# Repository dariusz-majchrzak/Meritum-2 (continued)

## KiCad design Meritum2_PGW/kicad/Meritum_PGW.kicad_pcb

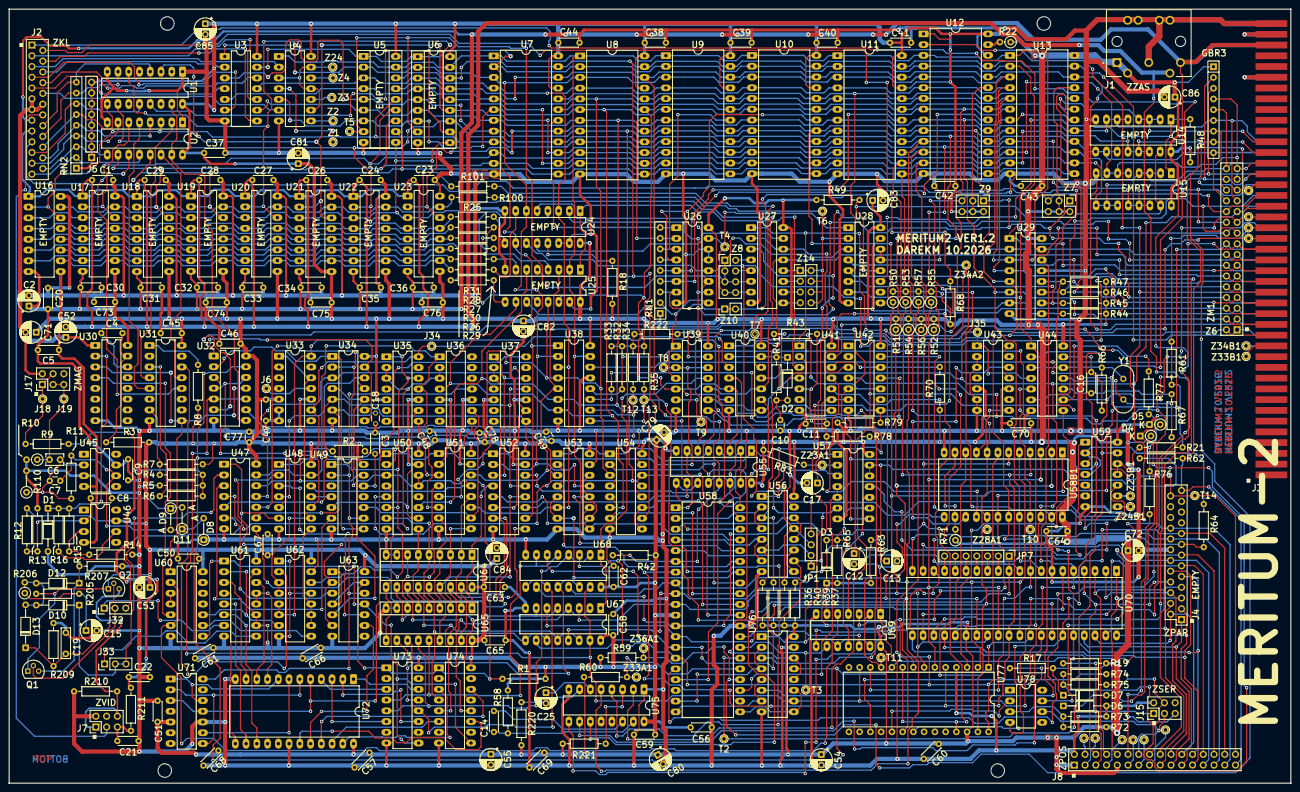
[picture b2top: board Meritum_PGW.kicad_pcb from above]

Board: 4 copper layers, 303.0 x 183.0 mm, 331 parts (0 on the bottom side), 330 nets.

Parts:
C1, C20, C23, C24, C26, C27, C28, C29, C30, C31, C32, C33, C34, C35, C36, C37, C38, C39, C40, C41, C42, C43, C44, C45, C46, C47, C50, C51, C56, C57, C58, C59, C60, C61, C62, C63, C64, C65, C66, C67, C68, C69, C70, C73, C74, C75, C76: 100n; c_200
C2, C12, C13, C17, C52, C53, C54, C55, C71, C72, C79, C80, C81, C82, C83, C84, C85, C86: 100uF; CP_Radial_D5.0mm_P2.50mm
C3, C11, C14, C16: 1n; c_200
C4: 33n; c_200
C5: 1u; c_200
C6: 10n; C_Rect_L4.0mm_W2.5mm_P2.50mm
C7: 330P; c_100
C8: 4u7; c_200
C9, C21, C22: 47n; c_200
C10: 470pF; c_100
C15: 22uF; CP_Radial_D5.0mm_P2.50mm
C18: 4n7; c_100
C19: 12p; C_Rect_L7.0mm_W2.0mm_P5.00mm
C25: 68uF; CP_Radial_D5.0mm_P2.50mm
C48, C49, C77, C78: 100n; c_100
D1, D2: 1N4148; D_DO-35_SOD27_P10.16mm_Horizontal
D3: BAYP95A; D_DO-35_SOD27_P10.16mm_Horizontal
D4, D5: 1N4148WT; D_DO-35_SOD27_P2.54mm_Vertical_KathodeUp
D6, D7, D10, D12, D13: 1N4148WT; D_DO-35_SOD27_P10.16mm_Horizontal
D8, D9, D11: 1N4148; D_DO-35_SOD27_P5.08mm_Vertical_AnodeUp
GBR3: 1K; R_Array_SIP9
J1: ZAS; CUI_SDS-50J
J2: ZKL; PinSocket_25_P2.54mm_Vertical
J3: ZM; Meritum_ZM
J4: ZPAR; PinSocket_25_P2.54mm_Vertical
J5: I; PinHeader_1x08_P2.54mm_Vertical
J6, J18, J19, J34, J35: T18; pin
J7: ZVID; PinHeader_2x03_P2.54mm_Vertical
J8: ZPOS; PinSocket_2x16_P2.54mm_Vertical_Meritum
J15: ZSER1; PinHeader_2x03_P2.54mm_Vertical
J17: ZMAG; PinHeader_2x03_P2.54mm_Vertical
J32, J33: Conn_01x03; PinHeader_1x03_P2.54mm_Vertical
JP1: Conn_01x04; PinHeader_1x04_P2.54mm_Vertical
JP7: Conn_01x07; PinHeader_1x07_P2.54mm_Vertical
Q1, Q2: BC550; TO-92L
R1, R8, R17, R19, R21, R32, R33, R34, R35, R36, R37, R39, R40, R44, R45, R46, R47, R48, R49, R64, R68, R70, R75, R79, R83, R221, R222: 1K; r_400
R2: 100; R_Axial_DIN0207_L6.3mm_D2.5mm_P7.62mm_Horizontal
R3, R220: 36K; r_400
R4, R6: 7K5; r_400
R5: 1K2; r_400
R7: 240k; r_400
R9, R72: 3K3; r_400
R10: 91K; R_Axial_DIN0207_L6.3mm_D2.5mm_P2.54mm_Vertical
R11: 240K; r_400
R12: 6K8; r_400
R13: 110; r_400
R14: 390; r_400
R15: 47K; r_400
R16: 150; r_400
R18, R58, R63, R65, R78: 10K; r_400
R22, R71: 1K; R_Axial_DIN0207_L6.3mm_D2.5mm_P2.54mm_Vertical
R25, R26, R27, R28, R29, R30, R31, R100, R101: 22; r_400
R41: 10k; r_400
R42, R66, R67: 330; r_400
R43, R62: 220; r_400
R50, R51, R52, R53, R54, R55, R56, R57: 15K; R_Axial_DIN0207_L6.3mm_D2.5mm_P2.54mm_Vertical
R59, R60, R209: 4K7; r_400
R61: 4k7; r_400
R73: 1K6; r_400
R74: 5K1; r_400
R76, R77: 270; r_400
R110: 4k7; R_Axial_DIN0207_L6.3mm_D2.5mm_P5.08mm_Vertical
R205: 2K2; r_400
R206: 2K2; R_Axial_DIN0207_L6.3mm_D2.5mm_P2.54mm_Vertical
R207: 2K; r_400
R210, R211: 100; r_400
RN1, RN2: 1K; R_Array_SIP9
T1, T4, T5, T6, T7, T8, T9, T10, T11, T12, T13, T14, T15, T16, T17, T18, T19: T18; pin
T2, T3: TP; pin
U1, U2, U67, U68: 8226; DIP-16_W7.62mm_LongPads
U3, U4, U42: 74LS06; DIP-14_W7.62mm_LongPads
U5, U6, U64, U65: 2114; DIP-18_W7.62mm_Socket_LongPads
U7, U8, U9, U10, U11, U13: 2716; DIP-24_W15.24mm_LongPads
U12: 2764_v1; DIP-28_W15.24mm_LongPads
U14, U15, U53, U54, U55, U56, U76: 8216; DIP-16_W7.62mm_LongPads
U16, U17, U18, U19, U20, U21, U22, U23: MK4116N; DIP-16_W7.62mm_LongPads
U24, U25, U50, U51, U52: 74LS157; DIP-16_W7.62mm_LongPads
U26: 74S188; DIP-16_W7.62mm_LongPads
U27: 74LS155; DIP-16_W7.62mm_LongPads
U28, U29, U38: 74S287; DIP-16_W7.62mm_LongPads
U30, U75: 74LS123; DIP-16_W7.62mm_LongPads
U31, U73, U74: 74LS175; DIP-16_W7.62mm_LongPads
U32, U39: 74LS32; DIP-14_W7.62mm_LongPads
U33: 74LS92; DIP-14_W7.62mm_LongPads
U34: 74LS10; DIP-14_W7.62mm_LongPads
U35, U36, U37, U71: 74LS93; DIP-14_W7.62mm_LongPads
U40, U44, U47: 74LS04; DIP-14_W7.62mm_LongPads
U41, U57: 74LS132; DIP-14_W7.62mm_LongPads
U43: 74LS90; DIP-14_W7.62mm_LongPads
U45, U46, U78: LM741; DIP-8_W7.62mm_LongPads
U48: 74LS08; DIP-14_W7.62mm_LongPads
U49: 74LS20; DIP-14_W7.62mm_LongPads
U58: Z80CPU; DIP-40_W15.24mm_LongPads
U58B1: 8253; DIP-24_W15.24mm_LongPads
U59, U63: 74LS74; DIP-14_W7.62mm_LongPads
U60: 74LS00; DIP-14_W7.62mm_LongPads
U61: 74LS165; DIP-16_W7.62mm_LongPads
U62: 74LS153; DIP-16_W7.62mm_LongPads
U69: 74LS125; DIP-14_W7.62mm_LongPads
U70: 8255; DIP-40_W15.24mm_LongPads
U72: 2732; DIP-24_W15.24mm_LongPads
U77: P8251A; DIP-28_W15.24mm
Y1: 10MHz; Crystal_HC49-4H_Vertical
Z1, Z2, Z3, Z4, Z23A1, Z23B1, Z24, Z24B1, Z28A1, Z33A1, Z33B1, Z34A2, Z34B1, Z36A1, Z36B1, Z37B1, Z38B1, Z39B1: TP; pin
Z6: ZM1; PinSocket_2x16_P2.54mm_Vertical_Meritum
Z7: Z3; PinHeader_2x03_P2.54mm_Vertical
Z8, Z14: Conn_02x04_Odd_Even; PinHeader_2x04_P2.54mm_Vertical
Z9: Z4; PinHeader_2x03_P2.54mm_Vertical
Z10: Conn_01x02; PinHeader_1x02_P2.54mm_Vertical

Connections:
+5V: C37.1, C38.1, C39.1, C40.1, C41.1, C42.1, C43.1, C44.1, C45.1, C46.1, C47.1, C48.1, C49.1, C50.1, C51.1, C53.1, C54.1, C55.1, C56.1, C57.1, C58.1, C59.1, C60.1, C61.1, C62.1, C63.1, C64.1, C65.1, C66.1, C67.1, C68.1, C69.1, C70.1, C71.1, C72.1, C73.1, C74.1, C75.1, C76.1, C77.1, C78.1, C79.1, C80.1, C81.1, C82.1, C83.1, C84.1, C85.1, C86.1, D3.1 (K), D5.1 (K), D7.1 (K), GBR3.1 (common), J1.1, J1.4, J4.8, J5.1, J5.2, J5.3, J5.4, J5.5, J5.6, J5.7, J5.8, J8.1, J8.9, Q1.1 (C), Q2.1 (C), R1.1, R3.1, R7.1, R8.2, R12.1, R17.2, R18.2, R19.1, R21.1, R22.1, R32.1, R33.1, R34.1, R35.1, R36.1, R37.1, R39.1, R40.1, R42.1, R44.1, R45.1, R46.1, R47.1, R48.1, R49.1, R50.2, R51.2, R52.2, R53.2, R54.2, R55.2, R56.2, R57.2, R58.2, R59.1, R60.1, R61.1, R63.1, R64.1, R65.1, R68.1, R70.2, R71.1, R72.1, R78.1, R79.1, R83.1, R205.1, R220.2, R221.2, R222.1, RN1.1 (common), RN2.1 (common), U1.16 (VCC), U2.16 (VCC), U3.14 (VCC), U4.14 (VCC), U5.18 (VCC), U6.18 (VCC), U7.21 (VPP), U7.24 (VCC), U8.21 (VPP), U8.24 (VCC), U9.21 (VPP), U9.24 (VCC), U10.21 (VPP), U10.24 (VCC), U11.21 (VPP), U11.24 (VCC), U12.1 (VPP), U12.23 (A11), U12.26 (NC), U12.28 (VCC), U13.21 (VPP), U13.24 (VCC), U14.16 (VCC), U15.16 (VCC), U16.9 (VCC), U17.9 (VCC), U18.9 (VCC), U19.9 (VCC), U20.9 (VCC), U21.9 (VCC), U22.9 (VCC), U23.9 (VCC), U24.16 (VCC), U25.16 (VCC), U26.16 (VCC), U27.16 (VCC), U28.16 (VCC), U29.16 (VCC), U30.16 (VCC), U31.16 (VCC), U32.14 (VCC), U33.5 (VCC), U34.14 (VCC), U35.5 (VCC), U36.5 (VCC), U37.5 (VCC), U38.16 (VCC), U39.14 (VCC), U40.14 (VCC), U41.14 (VCC), U42.14 (VCC), U43.5 (VCC), U44.14 (VCC), U46.7 (V+), U47.14 (VCC), U48.14 (VCC), U49.14 (VCC), U50.16 (VCC), U51.16 (VCC), U52.16 (VCC), U53.16 (VCC), U54.16 (VCC), U55.16 (VCC), U56.16 (VCC), U57.14 (VCC), U58.11 (VCC), U58B1.24 (VCC), U59.14 (VCC), U60.14 (VCC), U61.16 (VCC), U62.16 (VCC), U63.14 (VCC), U64.18 (VCC), U65.18 (VCC), U67.16 (VCC), U68.16 (VCC), U69.14 (VCC), U70.26 (VCC), U71.5 (VCC), U72.24 (VCC), U73.16 (VCC), U74.16 (VCC), U75.16 (VCC), U76.16 (VCC), U77.26 (VCC), Z7.2, Z7.3, Z7.4, Z7.6, Z9.2, Z9.3, Z9.4, Z9.6
+6V: J3.A42 (Pin_a42), J3.B42 (Pin_b42)
+12V: C2.1, C5.1, C9.2, C20.1, C22.1, C30.1, C31.1, C32.1, C33.1, C34.1, C35.1, C36.1, J1.3, J2.8, J3.A41 (Pin_a41), J3.B41 (Pin_b41), R211.2, U16.8 (VDD), U17.8 (VDD), U18.8 (VDD), U19.8 (VDD), U20.8 (VDD), U21.8 (VDD), U22.8 (VDD), U23.8 (VDD), U45.7 (V+), U78.7 (V+)
-5V: C1.2, C5.2, C23.2, C24.2, C26.2, C27.2, C28.2, C29.2, C52.2, J1.5, J2.9, U16.1 (VBB), U17.1 (VBB), U18.1 (VBB), U19.1 (VBB), U20.1 (VBB), U21.1 (VBB), U22.1 (VBB), U23.1 (VBB), U45.4 (V-), U46.4 (V-), U78.4 (V-)
-6V: J3.A38 (Pin_a38), J3.B38 (Pin_b38)
/CPU/Z0: U54.12 (DI3), U54.14 (DO3), U58.30 (A0)
/CPU/Z1: U54.9 (DI2), U54.11 (DO2), U58.31 (A1)
/CPU/Z2: U54.5 (DO1), U54.7 (DI1), U58.32 (A2)
/CPU/Z3: U54.2 (DO0), U54.4 (DI0), U58.33 (A3)
/CPU/Z4: U53.5 (DO1), U53.7 (DI1), U58.34 (A4)
/CPU/Z5: U53.2 (DO0), U53.4 (DI0), U58.35 (A5)
/CPU/Z6: U53.12 (DI3), U53.14 (DO3), U58.36 (A6)
/CPU/Z7: U53.9 (DI2), U53.11 (DO2), U58.37 (A7)
/CPU/Z8: U55.9 (DI2), U55.11 (DO2), U58.38 (A8)
/CPU/Z9: U55.12 (DI3), U55.14 (DO3), U58.39 (A9)
/CPU/Z10: U55.2 (DO0), U55.4 (DI0), U58.40 (A10)
/CPU/Z11: U55.5 (DO1), U55.7 (DI1), U58.1 (A11)
/CPU/Z12: U56.2 (DO0), U56.4 (DI0), U58.2 (A12)
/CPU/Z13: U56.12 (DI3), U56.14 (DO3), U58.3 (A13)
/CPU/Z14: U56.5 (DO1), U56.7 (DI1), U58.4 (A14)
/CPU/Z15: U56.9 (DI2), U56.11 (DO2), U58.5 (A15)
/Display/BLANK: U63.9 (Q), U72.20 (~OE/VPP)
/Display/DD0: U65.14 (D0), U68.5 (DO1), U68.7 (DI1), U73.4 (D0)
/Display/DD1: U65.13 (D1), U68.2 (DO0), U68.4 (DI0), U73.5 (D1)
/Display/DD2: U65.12 (D2), U68.9 (DI2), U68.11 (DO2), U73.12 (D2)
/Display/DD3: U65.11 (D3), U68.12 (DI3), U68.14 (DO3), U73.13 (D3)
/Display/DD4: U64.14 (D0), U67.9 (DI2), U67.11 (DO2), U74.4 (D0)
/Display/DD5: U64.13 (D1), U67.12 (DI3), U67.14 (DO3), U74.5 (D1)
/Display/DD6: U64.12 (D2), U67.2 (DO0), U67.4 (DI0), U74.12 (D2)
/Display/DD7: U64.11 (D3), U67.5 (DO1), U67.7 (DI1), U74.13 (D3)
/Display/L0: U71.1 (CP1..3), U71.12 (Q0), U72.8 (A0)
/Display/L1: U71.9 (Q1), U72.7 (A1)
/Display/L2: U71.2 (R0(1)), U71.8 (Q2), U72.6 (A2)
/Display/L3: U37.14 (CP0), U71.3 (R0(2)), U71.11 (Q3), U72.5 (A3)
/Display/MA0: U50.7 (Zb), U64.5 (A0), U65.5 (A0)
/Display/MA1: U50.9 (Zc), U64.6 (A1), U65.6 (A1)
/Display/MA2: U51.4 (Za), U64.7 (A2), U65.7 (A2)
/Display/MA3: U51.7 (Zb), U64.4 (A3), U65.4 (A3)
/Display/MA4: U51.9 (Zc), U64.3 (A4), U65.3 (A4)
/Display/MA5: U51.12 (Zd), U64.2 (A5), U65.2 (A5)
/Display/MA6: U52.4 (Za), U64.1 (A6), U65.1 (A6)
/Display/MA7: U52.7 (Zb), U64.17 (A7), U65.17 (A7)
/Display/MA8: U52.9 (Zc), U64.16 (A8), U65.16 (A8)
/Display/MA9: U52.12 (Zd), U64.15 (A9), U65.15 (A9)
/Display/NET_R1: R1.2, U34.2, U50.3 (I1a), U50.13 (I1d), U50.14 (I0d), U63.1 (~R), U63.4 (~S), U63.13 (~R), U73.1 (~Mr), U74.1 (~Mr)
/Display/SYNC: J32.3, U47.1, U48.6
/Display/VID_OUT: J7.1, J7.6, Q2.3 (E), R210.1
/Display/X0: U35.1 (CP1..3), U35.12 (Q0), U49.1, U50.6 (I1b), U62.14 (S0)
/Display/X1: U35.9 (Q1), U49.5, U50.10 (I1c)
/Display/X2: U35.8 (Q2), U51.3 (I1a)
/Display/X3: U35.11 (Q3), U36.1 (CP1..3), U47.13, U48.13, U51.6 (I1b)
/Display/X4: U36.9 (Q1), U49.10, U51.10 (I1c)
/Display/X5: U36.8 (Q2), U48.12, U51.13 (I1d)
/Display/X6: U37.1 (CP1..3), U37.12 (Q0), U52.3 (I1a)
/Display/X7: U34.3, U37.9 (Q1), U47.11, U52.6 (I1b)
/Display/X8: U34.9, U37.8 (Q2), U52.10 (I1c)
/Display/X9: U34.5, U37.11 (Q3), U47.5, U52.13 (I1d)
/Display/Y1: U36.11 (Q3), U49.2, U49.9, U63.12 (D), U71.14 (CP0)
/Display/Y2: U34.4, U34.10, U63.5 (Q)
/Display/~LOAD: U60.8, U61.1 (~PL), U63.11 (C), U73.9 (Cp), U74.9 (Cp)
/Display/~Y2: U48.2, U63.2 (D), U63.6 (~Q)
/Interface/CTS: J8.16, J15.4, R75.1
/Interface/KA0: J2.5, U3.4
/Interface/KA1: J2.15, U3.8
/Interface/KA2: J2.18, U4.6
/Interface/KA3: J2.4, U3.6
/Interface/KA4: J2.2, U3.10
/Interface/KA5: J2.16, U3.2
/Interface/KA6: J2.17, U3.12
/Interface/KA7: J2.3, U4.2
/Interface/KD0: J2.24, RN2.5 (R4), U2.4 (DI0)
/Interface/KD1: J2.12, RN2.4 (R3), U2.7 (DI1)
/Interface/KD2: J2.25, RN2.3 (R2), U2.9 (DI2)
/Interface/KD3: J2.13, RN2.2 (R1), U2.12 (DI3)
/Interface/KD4: J2.22, RN2.8 (R7), U1.7 (DI1)
/Interface/KD5: J2.21, RN2.9 (R8), U1.4 (DI0)
/Interface/KD6: J2.23, RN2.6 (R5), U1.9 (DI2)
/Interface/KD7: J2.11, RN2.7 (R6), U1.12 (DI3)
/Interface/PA0: J4.17, J8.6, U70.4 (PA0)
/Interface/PA1: J4.4, J8.8, U70.3 (PA1)
/Interface/PA2: J4.16, J8.20, U70.2 (PA2)
/Interface/PA3: J4.3, J8.10, U70.1 (PA3)
/Interface/PA4: J4.2, J8.21, U70.40 (PA4)
/Interface/PA5: J4.15, J8.17, U70.39 (PA5)
/Interface/PA6: J4.14, J8.22, U70.38 (PA6)
/Interface/PA7: J4.1, J8.19, U70.37 (PA7)
/Interface/PB0: J4.9, J8.30, U70.18 (PB0)
/Interface/PB1: J4.7, J8.28, U70.19 (PB1)
/Interface/PB2: J4.21, J8.27, U70.20 (PB2)
/Interface/PB3: J4.22, J8.29, U70.21 (PB3)
/Interface/PB4: J4.6, J8.26, U70.22 (PB4)
/Interface/PB5: J4.19, J8.25, U70.23 (PB5)
/Interface/PB6: J4.18, J8.23, U70.24 (PB6)
/Interface/PB7: J4.5, J8.24, U70.25 (PB7)
/Interface/PC0: J8.4, JP7.4, T15.1 (Pin_1_1), U70.14 (PC0)
/Interface/PC1: J8.3, JP7.5, T1.1 (Pin_1_1), U70.15 (PC1)
/Interface/PC2: J8.13, JP7.6, T17.1 (Pin_1_1), U70.16 (PC2)
/Interface/PC3: J8.7, JP7.7, T16.1 (Pin_1_1), U70.17 (PC3)
/Interface/PC4: J8.11, JP7.3, T18.1 (Pin_1_1), U70.13 (PC4)
/Interface/PC5: J8.15, JP7.2, T19.1 (Pin_1_1), U70.12 (PC5)
/Interface/PC6: JP7.1, U70.11 (PC6), U75.11 (Clr)
/Interface/PC7: U42.13, U70.10 (PC7)
/Interface/R1K: J8.5, J15.1, R19.2
/Interface/REC: J8.12, J15.5, R76.1
/Interface/SIG_IN: C6.1, J17.3, J17.5, J19.1 (Pin_1_1), R10.1
/Interface/SIG_OUT: J17.1, J17.4, J18.1 (Pin_1_1), R9.1
/Interface/TR: J8.14, J15.3, U78.6
/MEM/E0: R31.1, U16.5 (A0), U17.5 (A0), U18.5 (A0), U19.5 (A0), U20.5 (A0), U21.5 (A0), U22.5 (A0), U23.5 (A0)
/MEM/E1: R30.1, U16.7 (A1), U17.7 (A1), U18.7 (A1), U19.7 (A1), U20.7 (A1), U21.7 (A1), U22.7 (A1), U23.7 (A1)
/MEM/E2: R29.1, U16.6 (A2), U17.6 (A2), U18.6 (A2), U19.6 (A2), U20.6 (A2), U21.6 (A2), U22.6 (A2), U23.6 (A2)
/MEM/E3: R28.1, U16.12 (A3), U17.12 (A3), U18.12 (A3), U19.12 (A3), U20.12 (A3), U21.12 (A3), U22.12 (A3), U23.12 (A3)
/MEM/E4: R27.1, U16.11 (A4), U17.11 (A4), U18.11 (A4), U19.11 (A4), U20.11 (A4), U21.11 (A4), U22.11 (A4), U23.11 (A4)
/MEM/E5: R26.1, U16.10 (A5), U17.10 (A5), U18.10 (A5), U19.10 (A5), U20.10 (A5), U21.10 (A5), U22.10 (A5), U23.10 (A5)
/MEM/E6: R25.1, U16.13 (A6), U17.13 (A6), U18.13 (A6), U19.13 (A6), U20.13 (A6), U21.13 (A6), U22.13 (A6), U23.13 (A6)
/MEM/U27P15: U24.12 (Zd), U27.15 (Eb2)
/MEM/~M1CS: RN1.9 (R8), U7.18 (~EP), U26.1 (Q0)
/MEM/~M2CS: RN1.8 (R7), U8.18 (~EP), U26.2 (Q1)
/MEM/~M3CS: RN1.7 (R6), U9.18 (~EP), U26.3 (Q2)
/MEM/~M4CS: RN1.6 (R5), U10.18 (~EP), U26.4 (Q3)
/MEM/~M5CS: RN1.5 (R4), U11.18 (~EP), U26.5 (Q4)
/MEM/~M6CS: RN1.4 (R3), U12.20 (~CE), U26.6 (Q5)
/MEM/~M7CS: RN1.3 (R2), U13.18 (~EP), U26.7 (Q6), Z10.1, Z10.2
/MEM/~RAS: R101.2, U16.4 (~RAS), U17.4 (~RAS), U18.4 (~RAS), U19.4 (~RAS), U20.4 (~RAS), U21.4 (~RAS), U22.4 (~RAS), U23.4 (~RAS)
A0: J3.B14 (Pin_b14), U3.3, U5.5 (A0), U6.5 (A0), U7.8 (A0), U8.8 (A0), U9.8 (A0), U10.8 (A0), U11.8 (A0), U12.10 (A0), U13.8 (A0), U25.3 (I1a), U29.5 (A0), U38.5 (A0), U50.5 (I0b), U54.13 (DB3), U58B1.19 (A0), U70.9 (A0), U77.12 (C/~D), Z6.2
A1: J3.B15 (Pin_b15), U3.9, U5.6 (A1), U6.6 (A1), U7.7 (A1), U8.7 (A1), U9.7 (A1), U10.7 (A1), U11.7 (A1), U12.9 (A1), U13.7 (A1), U25.6 (I1b), U29.6 (A1), U38.6 (A1), U50.11 (I0c), U54.10 (DB2), U58B1.20 (A1), U70.8 (A1), Z6.4
A2: J3.B16 (Pin_b16), U4.5, U5.7 (A2), U6.7 (A2), U7.6 (A2), U8.6 (A2), U9.6 (A2), U10.6 (A2), U11.6 (A2), U12.8 (A2), U13.6 (A2), U25.10 (I1c), U29.7 (A2), U38.7 (A2), U51.2 (I0a), U54.6 (DB1), Z6.6
A3: J3.B17 (Pin_b17), U3.5, U5.4 (A3), U6.4 (A3), U7.5 (A3), U8.5 (A3), U9.5 (A3), U10.5 (A3), U11.5 (A3), U12.7 (A3), U13.5 (A3), U25.13 (I1d), U29.4 (A3), U38.4 (A3), U51.5 (I0b), U54.3 (DB0), Z6.7
A4: J3.B18 (Pin_b18), U3.11, U5.3 (A4), U6.3 (A4), U7.4 (A4), U8.4 (A4), U9.4 (A4), U10.4 (A4), U11.4 (A4), U12.6 (A4), U13.4 (A4), U24.3 (I1a), U29.3 (A4), U38.3 (A4), U51.11 (I0c), U53.6 (DB1), Z6.10
A5: J3.B19 (Pin_b19), U3.1, U5.2 (A5), U6.2 (A5), U7.3 (A5), U8.3 (A5), U9.3 (A5), U10.3 (A5), U11.3 (A5), U12.5 (A5), U13.3 (A5), U24.6 (I1b), U29.2 (A5), U38.2 (A5), U51.14 (I0d), U53.3 (DB0), Z6.12
A6: J3.B20 (Pin_b20), U3.13, U5.1 (A6), U6.1 (A6), U7.2 (A6), U8.2 (A6), U9.2 (A6), U10.2 (A6), U11.2 (A6), U12.4 (A6), U13.2 (A6), U24.10 (I1c), U29.1 (A6), U38.1 (A6), U52.2 (I0a), U53.13 (DB3), Z6.13
A7: J3.B21 (Pin_b21), U4.1, U5.17 (A7), U6.17 (A7), U7.1 (A7), U8.1 (A7), U9.1 (A7), U10.1 (A7), U11.1 (A7), U12.3 (A7), U13.1 (A7), U25.2 (I0a), U29.15 (A7), U38.15 (A7), U52.5 (I0b), U53.10 (DB2), Z6.16
A8: J3.A14 (Pin_a14), U5.16 (A8), U6.16 (A8), U7.23 (A8), U8.23 (A8), U9.23 (A8), U10.23 (A8), U11.23 (A8), U12.25 (A8), U13.23 (A8), U25.5 (I0b), U52.11 (I0c), U55.10 (DB2), Z6.1
A9: J3.A15 (Pin_a15), U5.15 (A9), U6.15 (A9), U7.22 (A9), U8.22 (A9), U9.22 (A9), U10.22 (A9), U11.22 (A9), U12.24 (A9), U13.22 (A9), U25.11 (I0c), U52.14 (I0d), U55.13 (DB3), Z6.3
A10: J3.A16 (Pin_a16), U7.19 (A10), U8.19 (A10), U9.19 (A10), U10.19 (A10), U11.19 (A10), U12.21 (A10), U13.19 (A10), U25.14 (I0d), U39.5, U40.5, U55.3 (DB0), Z6.5
A11: J3.A17 (Pin_a17), U24.2 (I0a), U26.10 (A0), U55.6 (DB1), Z6.8, Z7.1, Z9.1
A12: J3.A18 (Pin_a18), JP1.4, R40.2, U12.2 (A12), U24.5 (I0b), U26.11 (A1), U56.3 (DB0), Z6.9
A13: J3.A19 (Pin_a19), JP1.3, R39.2, U24.11 (I0c), U26.12 (A2), U56.13 (DB3), Z6.11
A14: J3.A20 (Pin_a20), JP1.2, R36.2, U27.13 (A0), U56.6 (DB1), Z6.14
A15: J3.A21 (Pin_a21), JP1.1, R37.2, U27.3 (A1), U56.10 (DB2), Z6.15
BD0: GBR3.2 (R1), J3.B29 (Pin_b29), R57.1, U2.3 (DB0), U5.14 (D0), U7.9 (Q0), U8.9 (Q0), U9.9 (Q0), U10.9 (Q0), U11.9 (Q0), U12.11 (D0), U13.9 (Q0), U15.12 (DI3), U15.13 (DB3), U15.14 (DO3), U16.2 (DIN), U16.14 (DOUT), U58.14 (D0), U58B1.8 (D0), U68.6 (DB1), U70.34 (D0), U77.27 (D0), Z6.30
BD1: GBR3.4 (R3), J3.B30 (Pin_b30), R56.1, U2.6 (DB1), U5.13 (D1), U7.10 (Q1), U8.10 (Q1), U9.10 (Q1), U10.10 (Q1), U11.10 (Q1), U12.12 (D1), U13.10 (Q1), U15.5 (DO1), U15.6 (DB1), U15.7 (DI1), U17.2 (DIN), U17.14 (DOUT), U58.15 (D1), U58B1.7 (D1), U68.3 (DB0), U70.33 (D1), U77.28 (D1), Z6.31
BD2: GBR3.8 (R7), J3.B31 (Pin_b31), R55.1, U2.10 (DB2), U5.12 (D2), U7.11 (Q2), U8.11 (Q2), U9.11 (Q2), U10.11 (Q2), U11.11 (Q2), U12.13 (D2), U13.11 (Q2), U14.12 (DI3), U14.13 (DB3), U14.14 (DO3), U18.2 (DIN), U18.14 (DOUT), U58.12 (D2), U58B1.6 (D2), U68.10 (DB2), U70.32 (D2), U77.1 (D2), Z6.27
BD3: GBR3.7 (R6), J3.B32 (Pin_b32), R54.1, U2.13 (DB3), U5.11 (D3), U7.13 (Q3), U8.13 (Q3), U9.13 (Q3), U10.13 (Q3), U11.13 (Q3), U12.15 (D3), U13.13 (Q3), U14.2 (DO0), U14.3 (DB0), U14.4 (DI0), U19.2 (DIN), U19.14 (DOUT), U58.8 (D3), U58B1.5 (D3), U68.13 (DB3), U70.31 (D3), U77.2 (D3), Z6.28
BD4: GBR3.3 (R2), J3.A29 (Pin_a29), R53.1, U1.6 (DB1), U6.14 (D0), U7.14 (Q4), U8.14 (Q4), U9.14 (Q4), U10.14 (Q4), U11.14 (Q4), U12.16 (D4), U13.14 (Q4), U15.9 (DI2), U15.10 (DB2), U15.11 (DO2), U20.2 (DIN), U20.14 (DOUT), U58.7 (D4), U58B1.4 (D4), U67.10 (DB2), U70.30 (D4), U77.5 (D4), Z6.29
BD5: GBR3.5 (R4), J3.A30 (Pin_a30), R52.1, U1.3 (DB0), U6.13 (D1), U7.15 (Q5), U8.15 (Q5), U9.15 (Q5), U10.15 (Q5), U11.15 (Q5), U12.17 (D5), U13.15 (Q5), U15.2 (DO0), U15.3 (DB0), U15.4 (DI0), U21.2 (DIN), U21.14 (DOUT), U58.9 (D5), U58B1.3 (D5), U67.13 (DB3), U70.29 (D5), U77.6 (D5), Z6.32
BD6: GBR3.9 (R8), J3.A31 (Pin_a31), R51.1, U1.10 (DB2), U6.12 (D2), U7.16 (Q6), U8.16 (Q6), U9.16 (Q6), U10.16 (Q6), U11.16 (Q6), U12.18 (D6), U13.16 (Q6), U14.9 (DI2), U14.10 (DB2), U14.11 (DO2), U22.2 (DIN), U22.14 (DOUT), U58.10 (D6), U58B1.2 (D6), U67.3 (DB0), U70.28 (D6), U77.7 (D6), Z6.26
BD7: GBR3.6 (R5), J3.A32 (Pin_a32), R50.1, U1.13 (DB3), U6.11 (D3), U7.17 (Q7), U8.17 (Q7), U9.17 (Q7), U10.17 (Q7), U11.17 (Q7), U12.19 (D7), U13.17 (Q7), U14.5 (DO1), U14.6 (DB1), U14.7 (DI1), U23.2 (DIN), U23.14 (DOUT), U58.13 (D7), U58B1.1 (D7), U67.6 (DB1), U69.6, U70.27 (D7), U77.8 (D7), Z6.25
BUC: J4.25, J8.32, R47.2, T14.1 (Pin_1_1), U29.12 (Q1)
BUSAK: U42.9, U53.1 (~CS), U54.1 (~CS), U55.1 (~CS), U57.6, U69.10, U69.13, U76.1 (~CS)
CKPIX: U60.10, U61.2 (CP), U62.7 (Za)
FON: J2.20, J7.3
GND: C1.1, C2.2, C3.2, C9.1, C10.2, C11.2, C12.2, C13.2, C15.2, C17.2, C18.2, C19.2, C20.2, C21.2, C22.2, C23.1, C24.1, C26.1, C27.1, C28.1, C29.1, C30.2, C31.2, C32.2, C33.2, C34.2, C35.2, C36.2, C37.2, C38.2, C39.2, C40.2, C41.2, C42.2, C43.2, C44.2, C45.2, C46.2, C47.2, C48.2, C49.2, C50.2, C51.2, C52.1, C53.2, C54.2, C55.2, C56.2, C57.2, C58.2, C59.2, C60.2, C61.2, C62.2, C63.2, C64.2, C65.2, C66.2, C67.2, C68.2, C69.2, C70.2, C71.2, C72.2, C73.2, C74.2, C75.2, C76.2, C77.2, C78.2, C79.2, C80.2, C81.2, C82.2, C83.2, C84.2, C85.2, C86.2, D1.2 (A), D4.2 (A), D6.2 (A), D8.1 (K), J1.2, J1.SH, J2.6, J2.7, J2.19, J3.A43 (Pin_a43), J3.B43 (Pin_b43), J4.20, J7.2, J8.2, J15.2, J17.2, R5.1, R10.2, R13.2, R14.2, R73.2, R110.2, R207.2, R209.2, R210.2, U1.1 (~CS), U1.8 (GND), U2.1 (~CS), U2.8 (GND), U3.7 (GND), U4.7 (GND), U5.9 (GND), U6.9 (GND), U7.12 (GND), U8.12 (GND), U9.12 (GND), U10.12 (GND), U11.12 (GND), U12.14 (GND), U13.12 (GND), U14.8 (GND), U15.8 (GND), U16.16 (VSS), U17.16 (VSS), U18.16 (VSS), U19.16 (VSS), U20.16 (VSS), U21.16 (VSS), U22.16 (VSS), U23.16 (VSS), U24.8 (GND), U24.14 (I0d), U24.15 (E), U25.8 (GND), U25.15 (E), U26.8 (GND), U26.13 (A3), U26.14 (A4), U27.8 (GND), U28.8 (GND), U28.13 (~CE1), U28.14 (~CE2), U29.8 (GND), U29.13 (~CE1), U30.1 (A), U30.8 (GND), U31.8 (GND), U32.7 (GND), U33.6 (R0(1)), U33.7 (R0(2)), U33.10 (GND), U34.7 (GND), U35.10 (GND), U36.10 (GND), U37.10 (GND), U38.8 (GND), U38.13 (~CE1), U39.7 (GND), U40.7 (GND), U41.7 (GND), U42.7 (GND), U43.2 (R0(1)), U43.3 (R0(2)), U43.6 (R9(1)), U43.7 (R9(2)), U43.10 (GND), U44.7 (GND), U45.3 (+), U47.7 (GND), U48.7 (GND), U49.7 (GND), U50.8 (GND), U50.15 (E), U51.8 (GND), U51.15 (E), U52.8 (GND), U52.15 (E), U53.8 (GND), U53.15 (~DIEN), U54.8 (GND), U54.15 (~DIEN), U55.8 (GND), U55.15 (~DIEN), U56.8 (GND), U56.15 (~DIEN), U57.7 (GND), U58.29 (GND), U58B1.12 (GND), U59.7 (GND), U60.7 (GND), U61.8 (GND), U61.10 (DS), U61.11 (D0), U61.15 (~CE), U62.1 (Ea), U62.8 (GND), U62.13 (I3b), U62.15 (Eb), U63.7 (GND), U64.8 (~CS), U64.9 (GND), U65.8 (~CS), U65.9 (GND), U67.8 (GND), U68.8 (GND), U69.1, U69.7 (GND), U70.7 (GND), U71.10 (GND), U72.12 (GND), U72.18 (~CE), U73.8 (GND), U74.8 (GND), U75.1 (A), U75.8 (GND), U76.8 (GND), U76.15 (~DIEN), U77.4 (GND)
IE: J3.B25 (Pin_b25), Z39B1.1 (Pin_1_1)
MON: U31.14 (~Q3), U62.2 (S1)
NMIX: J2.14, R68.2, U41.13
unnamed: C3.1, R2.2, U49.12
unnamed: C11.1, R43.1, U41.5
unnamed: C13.1, R62.2, R63.2, U57.12, U57.13
unnamed: C15.1, R205.2, R206.1
unnamed: C16.1, R67.2, U44.10
unnamed: C16.2, R66.1, U44.13
unnamed: C17.1, R78.2, U41.9, U42.6
unnamed: C18.1, U34.6, U47.9
unnamed: D1.1 (K), R15.2, R16.2, U30.2 (B)
unnamed: C10.1, D2.2 (A), R41.2, U41.2
unnamed: D2.1 (K), R41.1, U40.2, U40.13
unnamed: C12.1, D3.2 (A), R65.2, U57.9
unnamed: D4.1 (K), D5.2 (A), R74.1, R75.2
unnamed: D6.1 (K), D7.2 (A), R76.2, R77.1
unnamed: D10.2 (A), D12.2 (A), D13.2 (A), R206.2
unnamed: D10.1 (K), J33.2, J33.3, U47.2
unnamed: C8.2, D9.1 (K), D11.2 (A)
unnamed: C7.2, D8.2 (A), D9.2 (A), D11.1 (K), R11.2, U45.6
unnamed: D12.1 (K), Q1.3 (E), R207.1
unnamed: C19.1, D13.1 (K), Q2.2 (B), R209.1
unnamed: J6.1 (Pin_1_1), U33.11 (Q1)
unnamed: C21.1, J7.5, R211.1
unnamed: J32.1, J32.2, Q1.2 (B), U61.7 (~Q7)
unnamed: J33.1, U61.9 (Q7)
unnamed: J34.1 (Pin_1_1), U33.9 (Q2), U35.14 (CP0), U40.3, U48.10
unnamed: R2.1, U47.12, U49.13
unnamed: R4.1, R5.2, R6.1, R9.2
unnamed: R16.1, U46.6
unnamed: R66.2, U44.3, U44.12, Y1.1
unnamed: R67.1, U44.11, Y1.2
unnamed: R70.1, U41.12, U42.12
unnamed: R77.2, U44.9
unnamed: R222.2, U39.13, U42.10
unnamed: RN1.2 (R1), U26.9 (Q7), U39.1, U39.4
unnamed: T3.1 (Pin_1_1), U58.27 (~M1), U69.9
unnamed: R101.1, T7.1 (Pin_1_1), U40.12
unnamed: U1.15 (~DIEN), U2.15 (~DIEN), U32.8
unnamed: U2.2 (DO0), U31.4 (D0)
unnamed: U2.5 (DO1), U31.5 (D1)
unnamed: U2.11 (DO2), U31.12 (D2)
unnamed: U2.14 (DO3), U31.13 (D3)
unnamed: R22.2, U12.27 (~PGM)
unnamed: R48.2, U14.1 (~CS), U15.1 (~CS), U28.11 (Q2)
unnamed: R49.2, U14.15 (~DIEN), U15.15 (~DIEN), U28.12 (Q1)
unnamed: R18.1, U24.13 (I1d)
unnamed: U24.1 (S), U25.1 (S), U41.3
unnamed: R27.2, U24.4 (Za)
unnamed: R26.2, U24.7 (Zb)
unnamed: R25.2, U24.9 (Zc)
unnamed: R31.2, U25.4 (Za)
unnamed: R30.2, U25.7 (Zb)
unnamed: R29.2, U25.9 (Zc)
unnamed: R28.2, U25.12 (Zd)
unnamed: U27.9 (Q0b), Z14.7
unnamed: U27.10 (Q1b), Z14.5
unnamed: U27.5 (Q2a), Z8.4
unnamed: U27.11 (Q2b), Z14.3
unnamed: U27.4 (Q3a), Z8.2
unnamed: C4.1, U30.14 (Cext)
unnamed: U30.3 (Clr), U31.9 (Cp), U32.11, U60.1
unnamed: C4.2, R3.2, U30.15 (RCext)
unnamed: U30.4 (~Q), U60.5
unnamed: R4.2, R7.2, U31.7 (Q1)
unnamed: R8.1, U31.1 (~Mr)
unnamed: R6.2, U31.3 (~Q0)
unnamed: U32.1, U34.8, U34.13
unnamed: U32.2, U34.1, U49.8
unnamed: U32.3, U48.5
unnamed: U32.6, U69.4
unnamed: U33.1 (CP1..3), U33.12 (Q0), U48.9, U62.3 (I3a), U62.4 (I2a)
unnamed: U34.11, U47.10
unnamed: U34.12, U48.4
unnamed: U35.2 (R0(1)), U35.3 (R0(2)), U36.2 (R0(1)), U36.3 (R0(2)), U47.4
unnamed: U37.2 (R0(1)), U37.3 (R0(2)), U47.8
unnamed: U39.2, U40.6
unnamed: U39.8, U42.11
unnamed: U43.11 (Q3), U43.14 (CP0)
unnamed: U43.12 (Q0), U58B1.15 (CLK1)
unnamed: U43.8 (Q2), U58B1.9 (CLK0)
unnamed: C6.2, C7.1, R11.1, R110.1, U45.2 (-)
unnamed: R14.1, R15.1, U46.3 (+)
unnamed: C8.1, R12.2, R13.1, U46.2 (-)
unnamed: U47.3, U49.6
unnamed: U48.11, U49.4
unnamed: U50.4 (Za), U64.10 (~WE), U65.10 (~WE)
unnamed: U56.1 (~CS), U57.3
unnamed: U57.4, U57.5, U58.23 (~BUSACK)
unnamed: U58.20 (~IORQ), U76.5 (DO1), U76.7 (DI1)
unnamed: U58.19 (~MREQ), U76.2 (DO0), U76.4 (DI0)
unnamed: U58.21 (~RD), U76.9 (DI2), U76.11 (DO2)
unnamed: U58.28 (~RFSH), U69.12
unnamed: U40.9, U58.22 (~WR), U76.12 (DI3), U76.14 (DO3)
unnamed: R71.2, U58B1.11 (G0), U58B1.14 (G1)
unnamed: U41.11, U58B1.16 (G2)
unnamed: U58B1.13 (OUT1), U75.9 (A)
unnamed: U44.2, U59.3 (C)
unnamed: R64.2, U59.2 (D), U59.4 (~S)
unnamed: U59.5 (Q), U75.2 (B)
unnamed: U57.11, U59.1 (~R)
unnamed: R21.2, U59.11 (C), U59.12 (D)
unnamed: U59.9 (Q), Z23B1.1 (Pin_1_1)
unnamed: U59.8 (~Q), Z24B1.1 (Pin_1_1)
unnamed: U60.2, U60.6, U69.5
unnamed: U60.3, U60.4
unnamed: U61.12 (D1), U61.13 (D2), U72.9 (Q0)
unnamed: U61.14 (D3), U72.10 (Q1)
unnamed: U61.3 (D4), U72.11 (Q2)
unnamed: U61.4 (D5), U72.13 (Q3)
unnamed: U61.5 (D6), U72.14 (Q4)
unnamed: U61.6 (D7), U72.15 (Q5)
unnamed: U48.8, U62.10 (I0b), U62.11 (I1b), U62.12 (I2b)
unnamed: U60.9, U62.9 (Zb)
unnamed: U47.6, U63.3 (C)
unnamed: U48.3, U63.10 (~S)
unnamed: U39.11, U67.1 (~CS), U68.1 (~CS)
unnamed: U72.4 (A4), U73.3 (~Q0)
unnamed: U72.3 (A5), U73.6 (~Q1)
unnamed: U72.2 (A6), U73.11 (~Q2)
unnamed: U72.1 (A7), U73.14 (~Q3)
unnamed: U72.23 (A8), U74.3 (~Q0)
unnamed: U72.22 (A9), U74.6 (~Q1)
unnamed: U72.19 (A10), U74.11 (~Q2)
unnamed: U72.21 (A11), U74.14 (~Q3)
unnamed: C14.2, U75.14 (Cext)
unnamed: R221.1, U75.3 (Clr)
unnamed: C14.1, R58.1, U75.15 (RCext)
unnamed: U57.10, U75.4 (~Q)
unnamed: R17.1, U75.10 (B)
unnamed: C25.1, U75.6 (Cext)
unnamed: C25.2, R220.1, U75.7 (RCext)
unnamed: U44.8, U77.3 (RxD)
unnamed: U77.19 (TxD), U78.2 (-)
unnamed: R74.2, U77.17 (~CTS)
unnamed: R72.2, R73.1, U78.3 (+)
unnamed: U4.4, Z1.1 (Pin_1_1)
unnamed: U4.8, Z2.1 (Pin_1_1)
unnamed: U4.10, Z3.1 (Pin_1_1)
unnamed: U4.12, Z4.1 (Pin_1_1)
unnamed: R83.2, U57.2, Z23A1.1 (Pin_1_1)
unnamed: U4.3, U4.9, U4.11, U4.13, Z24.1 (Pin_1_1)
PHI_OSC: J35.1 (Pin_1_1), U33.14 (CP0), U43.1 (CP1..3), U44.4, U62.5 (I1a), U62.6 (I0a)
PHI_S: U58B1.10 (OUT0), U77.9 (~TxC), U77.25 (~RxC)
PHI_VID: R42.2, U40.4, U58.6 (~CLK), U69.2
RD: U5.10 (~WE), U6.10 (~WE), U16.3 (~WRITE), U17.3 (~WRITE), U18.3 (~WRITE), U19.3 (~WRITE), U20.3 (~WRITE), U21.3 (~WRITE), U22.3 (~WRITE), U23.3 (~WRITE), U39.10, U40.10
RESIN: J2.1, J4.13, J8.31, R62.1
RESOUT: U42.5, U44.5, U57.8, U70.35 (RESET), U77.21 (RESET)
TINT: U42.3, U75.5 (Q)
TNMI: U41.10, U58B1.17 (OUT2), Z28A1.1 (Pin_1_1)
WR: R43.2, U39.9, U40.8, U41.4
~BCS: J2.10, R45.2, U29.10 (Q3)
~BUSAK: J3.A13 (Pin_a13), R79.2, U28.4 (A3), U42.8, U57.1, Z34A2.1 (Pin_1_1), Z34B1.1 (Pin_1_1)
~BUSRQ: J3.B13 (Pin_b13), R60.2, U58.25 (~BUSRQ), Z33A1.1 (Pin_1_1), Z33B1.1 (Pin_1_1)
~CAS: R100.1, U16.15 (~CAS), U17.15 (~CAS), U18.15 (~CAS), U19.15 (~CAS), U20.15 (~CAS), U21.15 (~CAS), U22.15 (~CAS), U23.15 (~CAS)
~FDCS: J8.18, R46.2, U29.11 (Q2)
~INT: J3.B24 (Pin_b24), R61.2, U42.4, U58.16 (~INT), Z38B1.1 (Pin_1_1)
~IORQ: J3.A28 (Pin_a28), U28.6 (A1), U29.14 (~CE2), U38.14 (~CE2), U76.6 (DB1), Z6.22
~IOS: R44.2, U28.15 (A7), U29.9 (Q4)
~KL: T9.1 (Pin_1_1), U32.9, U39.6
~M1: J3.A24 (Pin_a24), U28.7 (A2), U44.1, U69.8, Z6.20
~MAG: R34.2, T12.1 (Pin_1_1), U32.4, U32.12, U38.10 (Q3)
~MREQ: J3.A27 (Pin_a27), U27.2 (Ea2), U27.14 (Eb1), U40.1, U76.3 (DB0), Z6.19
~NMI: J3.B23 (Pin_b23), U41.8, U58.17 (~NMI), Z37B1.1 (Pin_1_1)
~PCS: R35.2, T13.1 (Pin_1_1), U38.9 (Q4), U70.6 (~CS)
~PHI: J3.A22 (Pin_a22), U58B1.18 (CLK2), U69.3, U77.20 (CLK), Z6.18
~RAMSEL: R100.2, T6.1 (Pin_1_1), U27.12 (Q3b), U28.2 (A5), Z14.1, Z14.2, Z14.4, Z14.6, Z14.8
~RAMS: T5.1 (Pin_1_1), U5.8 (~CS), U6.8 (~CS), U27.6 (Q1a), U28.3 (A4), Z8.1, Z8.3, Z8.5, Z8.6
~RD: J3.A26 (Pin_a26), U7.20 (~G), U8.20 (~G), U9.20 (~G), U10.20 (~G), U11.20 (~G), U12.22 (~OE), U13.20 (~G), U28.5 (A0), U32.5, U32.10, U40.11, U58B1.22 (~RD), U67.15 (~DIEN), U68.15 (~DIEN), U70.5 (~RD), U76.10 (DB2), U77.13 (~RD), Z6.23
~RESOUT: J3.B26 (Pin_b26), T2.1 (Pin_1_1), U44.6, U58.26 (~RESET), U59.13 (~R), Z6.21
~RFSH: J3.B22 (Pin_b22), U27.1 (Ea1), U41.1, U69.11, Z6.17
~ROM: T4.1 (Pin_1_1), U26.15 (~G), U27.7 (Q0a), U28.1 (A6), Z8.7, Z8.8
~SCS: R33.2, T11.1 (Pin_1_1), U38.11 (Q2), U77.11 (~CS)
~TCS: R32.2, T10.1 (Pin_1_1), U38.12 (Q1), U58B1.21 (~CS)
~VID: T8.1 (Pin_1_1), U39.3, U39.12, U48.1, U50.1 (S), U51.1 (S), U52.1 (S)
~WAIT: J3.B28 (Pin_b28), R59.2, U58.24 (~WAIT), Z36A1.1 (Pin_1_1), Z36B1.1 (Pin_1_1)
~WR: J3.B27 (Pin_b27), U32.13, U50.2 (I0a), U58B1.23 (~WR), U59.10 (~S), U70.36 (~WR), U76.13 (DB3), U77.10 (~WR), Z6.24, Z7.5, Z9.5
